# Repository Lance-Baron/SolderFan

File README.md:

The goal of this project is to make my own solder fan, also sometimes called fume extractor. This started as I was shocked by the prices of filters, given that they are just a fan, and a filter. 

When doing research for this project, I also found the majority of them do not properly filter solder fumes out, as they use charcoal filters, not HEPA filters. I found that they do not filter out throught [this](https://www.sentryair.com/blog/industry-applications/soldering/comparing-solder-fume-extractors-its-all-about-the-filter/) link. Its a good read, and you can see I got many of my ideas from this article. 

To reduce prices, I just found a square [HEPA filter](https://www.amazon.com/20-81002-20-86883-Progressive-Whispertone-Panasonic/dp/B0CYC8G5DY?crid=1MQGWQIQ11IZC&dib=eyJ2IjoiMSJ9.4gcygidnoWYwowDgM76I_6dEPpSY0pNmuf3U-HRlpikCQP7qKgyJa00I6fX-hxttsFYL4-WjccQ20lXNSj4le4LuC1uzqhpPaounSTwANOWIDogZ6hMskyQ2XYOTo5oT0aG2jGo-3XQMuEb5qD6-tR9PRKeBTWpV0p9wItiHcaLFqXzdxAC8cu05e2CbstwPfd5I9145K-VNvcRMY9A8y-PB3iCnbgNQVMwLTIlcJjc.NOBcHMs9oRzRtBVV2toZYs6sPzAZyemaNt5jwrRnrI4&dib_tag=se&keywords=hepa+filter&qid=1771705624&sprefix=hepa+fil%2Caps%2C259&sr=8-2) on Amazon, as well as some standard 12V [computer fans](https://www.amazon.com/Strong-120x120x25mm-Computer-Cooling-1600RPM/dp/B07D493BDX?dib=eyJ2IjoiMSJ9.Fj1he09g2rYmTJk1keXhDAz0F9ZfC2FiD-CvyqoihXYhvo4hz7loQNC9NByMGLXPPuh_YLZb57zt8uVgY1q_57E-bY4g6VrGRKWQ4qmGfnp9p-HzLhNRJD6PlMVjIzGVUzEctj6X6e3wTnX0Ba1R1ahb3gQI_ICta_efkGT7buySdWxQTuOuBE8arY6ml29eVV3U8if8d8bK41HV8elJ-h6NsERoTy9oNpWc0BtKsyQ.J_YtjX3ok2GZddwHcR0QyvlmfVuZ6ghXbLYONCa1DEI&dib_tag=se&keywords=12v+computer+fan&qid=1771705651&sr=8-2). As they are already common parts the main body of the solder fan (at time of writitng) would be less than 10$.

Then in theory, I would just need to have some electronics to power the fan, and a case to hold it all together.

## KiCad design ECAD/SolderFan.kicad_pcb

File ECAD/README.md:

For the electrical section, the goal is powering the fan. The max recommended power is 3W, and it operates at 12V

`3W = 12V * I`

`3W / 12V = I`

`I = 0.25A`

So there is not alot of power that needs to be trasfered here. For this amount of power, USB-C is overkill, but it is a common cable, so I will use it for this project. The problem is USB-C, without PD, comes in at 5V. Thus we need a boost converter here aswell.

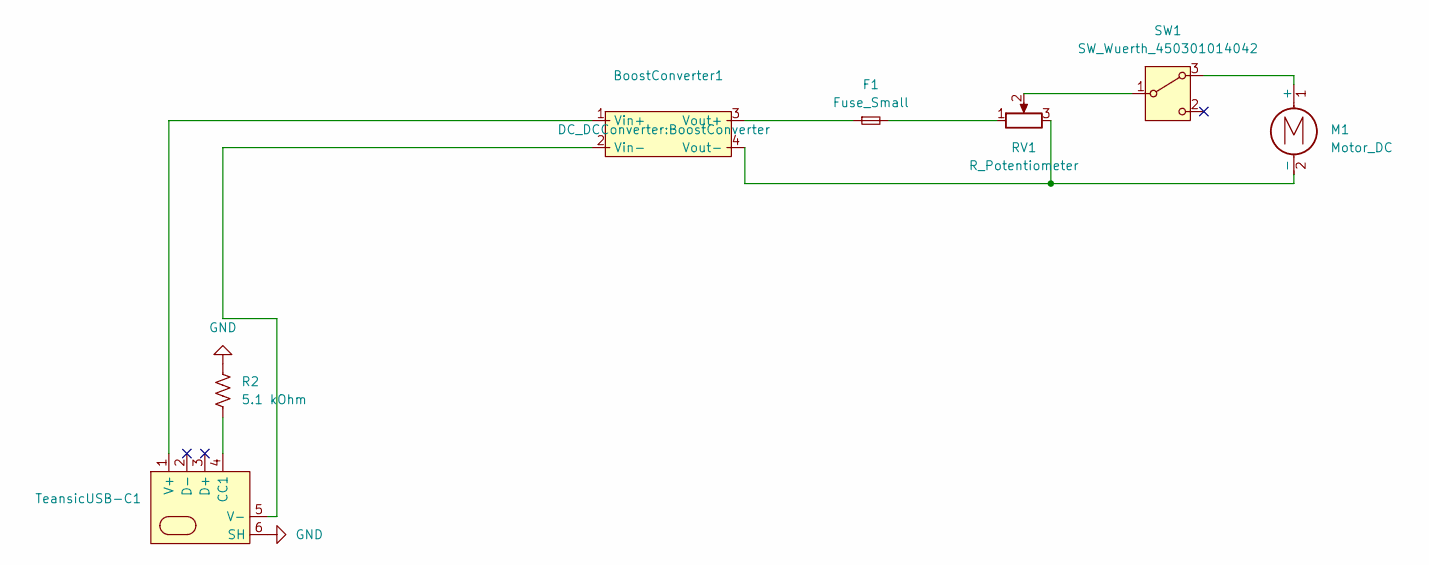
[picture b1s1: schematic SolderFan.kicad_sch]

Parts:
BoostConverter1: BoostConverter
F1: Fuse_Small; BLX-A Fuse Holder
M1: Motor_DC; JST_XH_B2B-XH-AM_1x02_P2.50mm_Vertical
R2: 5.1 kOhm; R_Axial_DIN0204_L3.6mm_D1.6mm_P5.08mm_Horizontal
RV1: R_Potentiometer; Taiss3PTHTPot
SW1: SW_Wuerth_450301014042; SW_Slide-03_Wuerth-WS-SLTV_10x2.5x6.4_P2.54mm
TeansicUSB-C1: TeansicUSB_C_6PIN

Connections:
GND: R2.1, TeansicUSB-C1.6 (SH)
unnamed: BoostConverter1.1 (Vin+), TeansicUSB-C1.1 (V+)
unnamed: BoostConverter1.2 (Vin-), TeansicUSB-C1.5 (V-)
unnamed: BoostConverter1.3 (Vout+), F1.1
unnamed: BoostConverter1.4 (Vout-), M1.2 (-), RV1.3
unnamed: F1.2, RV1.1
unnamed: M1.1 (+), SW1.3 (A)
unnamed: RV1.2, SW1.1 (B)
unnamed: R2.2, TeansicUSB-C1.4 (CC1)

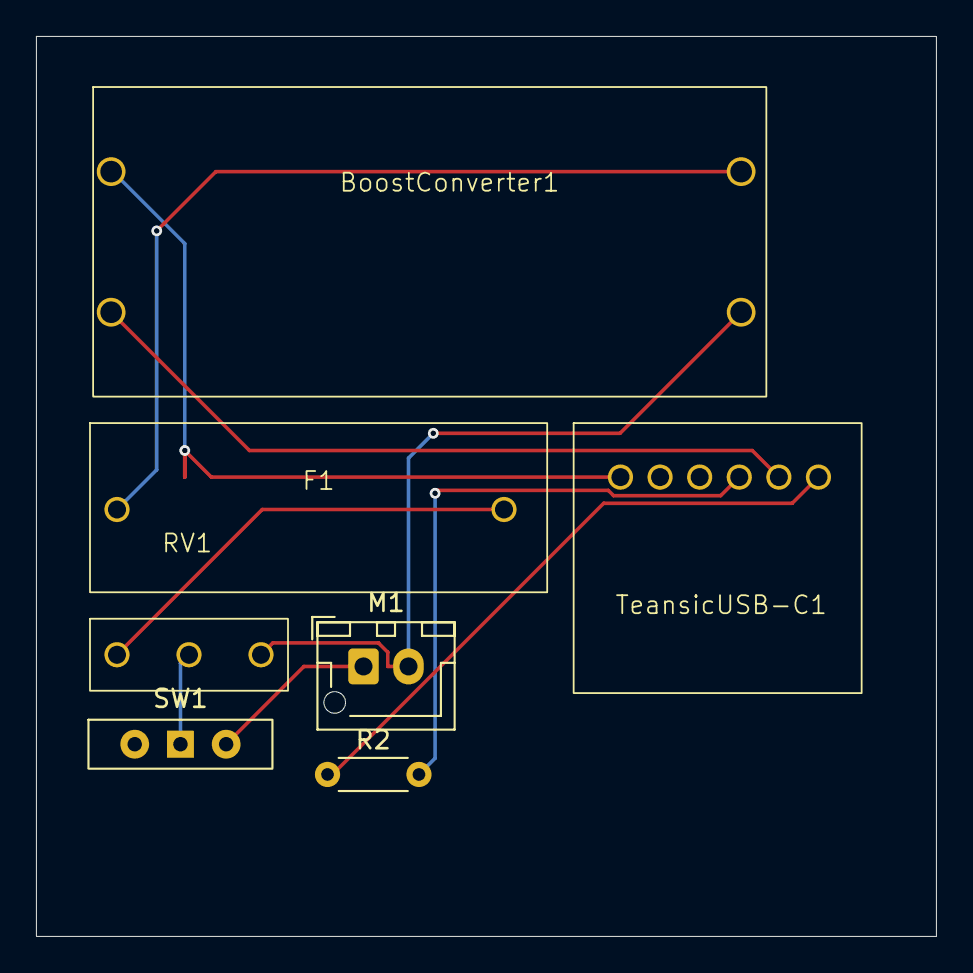
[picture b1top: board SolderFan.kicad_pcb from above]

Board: 2 copper layers, 50.0 x 50.0 mm, 7 parts (0 on the bottom side), 9 nets.

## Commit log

2026-02-21 Added CAD README
2026-02-21 Added img of fan to CAD README
2026-02-21 Added main README with project background
2026-02-21 Added Electrical README
2026-02-21 Updated gitignore to not track autosaves
2026-02-22 Updated Schematic, and PCB
